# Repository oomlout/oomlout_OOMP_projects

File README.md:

# oomlout_OOMP_projects
OOpen Organization Method for parts. This is all the project details.

### Part Files
* Summaries
	Readme's are generated using mdutils (https://github.com/didix21/mdutils). Generation is done in OOMPsummaries.py
	* Readme.md (generated)  --  A summary of the part in markdown.

* Images
	Images also have extra resolutions generated these are, _140, _450, _600.
	* image.jpg  --  Main image.
	* image_RE.jpg  --  Image for size reference (usually beside a sharpened pencil).
	* image_TOP.jpg  --  Image of the top of the part.
	* image_BOTTOM.jpg  --  Image of the bottom of the part.
	
* Diagrams
	Diagrams are generated from tags, they can use templates (templates/diag/), which can use a parts tags as input. These are compiled to a python script that uses the Simple Inkscape Scripting Extension (https://github.com/spakin/SimpInkScr/) to draw and save svgs, these svgs are then used to genearate pngs, dxfs, and pdfs.
	* diagBBLS.py (generated)  --  A diagram for adding a part to a breadboard layout sheet.
	* diagDIAG.py (generated)  --  A diagram for adding a part to a layout.
	* diagIDEN.py (generated)  --  A diagram for adding a part to a PCB with details.
	* diagSCHEM.py (generated)  --  A diagram for adding a part to a schematic.
	* diagSIMP.py (generated)  --  A diagram with only the parts outline, and link.
    * diagFritz.fzpz  --  A diagram in Fritzing format
    * working.cdr  --  A file for working on the component drawing in Corel Draw format

* Datasheets
	* datasheet.pdf  --  Datasheet for the part.
	* datasheet-C-SUPL  --  If more than one datasheet exists the manufacturers four letter code is added.
	* datasheet.txt (generated)  --  If the datasheet is a duplicate this file has the location in it, if it is hosted externally a link.
	
* 3D Models
	3D models are generated programatically these routines are in OOMPscad.py, they use SolidPython (https://github.com/SolidCode/SolidPython) to generate .scad files from which stls and pngs are generated.
	* 3dmodel.scad (generated)  --  Scad model of the part. Programatically generated in OOMPscad.py
	* 3dmodel.stl (generated)  --  STL version of 3dmodel.scad
	* 3dmodel.png (generated)  --  Rendered image of 3dmodel.scad (ortho)
	
* Labels
	Labels are generated using tags and templates these are in templates/label/ they are svgs and use search and replace to generate labels. (%%ID%% is replaced by part ID and tags are format @@%%ID%%,oompPart.oompID,tagName@@). From the svgs pdfs are generated.
	* label-front.svg (generated)  --  A label for the front of a bag.
	* label-inventory.svg (generated)  --  A label for keeping inventory organized.
	* label-spec.svg (generated)  --  A label listing part specifications.

* EDA
    Design files
    * boardEagle.brd  --  Board file in Eagle format
    * schematicEagle.scm  --  Schematic File in Eagle format
    * boardKicad.brd  --  Board file in Kicad format
    * schematicKicad.scm  --  Schematic File in Kicad format

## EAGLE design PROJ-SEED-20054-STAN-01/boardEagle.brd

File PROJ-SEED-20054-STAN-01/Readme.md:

Contents
========

* [PRS20054 > ](#prs20054--)
	* [Schematic](#schematic)
	* [Interactive BOM](#interactive-bom)
	* [OOMP Parts](#oomp-parts)
	* [Images](#images)
	* [Tags](#tags)
  
![][im]
# PRS20054 > 

- ID: PROJ-SEED-20054-STAN-01
- Hex ID: PRS20054
- Name: Grove - ADXL345 - 3-Axis Digital Accelerometer(+/-16g)
- Description: Grove - ADXL345 - 3-Axis Digital Accelerometer(+/-16g)
- Long Link: [http://oom.lt/PROJ-SEED-20054-STAN-01](http://oom.lt/PROJ-SEED-20054-STAN-01)
- Short Link: [http://oom.lt/PRS20054](http://oom.lt/PRS20054)

## Schematic

## Interactive BOM

- Interactive BOM page: [ibom.html](https://htmlpreview.github.io/?https://github.com/oomlout/oomlout_OOMP_projects/blob/main/PROJ-SEED-20054-STAN-01/kicad/bom/ibom.html)

## OOMP Parts

|OOMP ID|Name|Identifier|
| :---: | :---: | :---: |
|[CAPC-0805-X-UF10-V10](https://github.com/oomlout/oomlout_OOMP_parts/tree/main/CAPC-0805-X-UF10-V10/)|[SMD (0805) 10 uF Capacitor (Ceramic) 10v](https://github.com/oomlout/oomlout_OOMP_parts/tree/main/CAPC-0805-X-UF10-V10/)|[C5, C6](https://github.com/oomlout/oomlout_OOMP_parts/tree/main/CAPC-0805-X-UF10-V10/)|
|UNMATCHED-UNMATCHED-X-UNMATCHED-01||J1, P1, P4, P5, P6, TP1, TP2, TP3, TP4|
|UNMATCHED-SO23-X-UNMATCHED-01||Q1, Q2, U5|
|[RESE-0603-X-O472-01](https://github.com/oomlout/oomlout_OOMP_parts/tree/main/RESE-0603-X-O472-01/)|[SMD (0603) 4.7k Ohm Resistor](https://github.com/oomlout/oomlout_OOMP_parts/tree/main/RESE-0603-X-O472-01/)|[R2, R3, R4, R5](https://github.com/oomlout/oomlout_OOMP_parts/tree/main/RESE-0603-X-O472-01/)|
|[SENS-LG14-X-K345-01](https://github.com/oomlout/oomlout_OOMP_parts/tree/main/SENS-LG14-X-K345-01/)|[14 Pin SMD (LGA) Digital Accelerometer (ADXL345) Sensor](https://github.com/oomlout/oomlout_OOMP_parts/tree/main/SENS-LG14-X-K345-01/)|[U1](https://github.com/oomlout/oomlout_OOMP_parts/tree/main/SENS-LG14-X-K345-01/)|

## Images

|bominteractivefront|bominteractiveback|kicadPcb3d|kicadPcb3dFront|kicadPcb3dBack|eagleSchemImage|
| :---: | :---: | :---: | :---: | :---: | :---: |
|||||||

## Tags

- oompType: PROJ
- oompSize: SEED
- oompColor: 20054
- oompDesc: STAN
- oompIndex: 01
- name: Grove - ADXL345 - 3-Axis Digital Accelerometer(+/-16g)
- gitName: 
- hexID: PRS20054
- oompID: PROJ-SEED-20054-STAN-01
- oompParts: C5,CAPC-0805-X-UF10-V10
- oompParts: C6,CAPC-0805-X-UF10-V10
- oompParts: J1,UNMATCHED-UNMATCHED-X-UNMATCHED-01
- oompParts: P1,UNMATCHED-UNMATCHED-X-UNMATCHED-01
- oompParts: P4,UNMATCHED-UNMATCHED-X-UNMATCHED-01
- oompParts: P5,UNMATCHED-UNMATCHED-X-UNMATCHED-01
- oompParts: P6,UNMATCHED-UNMATCHED-X-UNMATCHED-01
- oompParts: Q1,UNMATCHED-SO23-X-UNMATCHED-01
- oompParts: Q2,UNMATCHED-SO23-X-UNMATCHED-01
- oompParts: R2,RESE-0603-X-O472-01
- oompParts: R3,RESE-0603-X-O472-01
- oompParts: R4,RESE-0603-X-O472-01
- oompParts: R5,RESE-0603-X-O472-01
- oompParts: TP1,UNMATCHED-UNMATCHED-X-UNMATCHED-01
- oompParts: TP2,UNMATCHED-UNMATCHED-X-UNMATCHED-01
- oompParts: TP3,UNMATCHED-UNMATCHED-X-UNMATCHED-01
- oompParts: TP4,UNMATCHED-UNMATCHED-X-UNMATCHED-01
- oompParts: U1,SENS-LG14-X-K345-01
- oompParts: U5,UNMATCHED-SO23-X-UNMATCHED-01
- rawParts: C5,10uF,C-0805,C0805,Ceramic Capacitors,,
- rawParts: C6,10uF,C-0805,C0805,Ceramic Capacitors,,
- rawParts: C7,DNP,CAP-AVX-A,AVX-A,Electrolytic Capacitors,Tantalum Capacitors and Super Capacitors,,
- rawParts: J1,SMD Grove,TWIG-4P-2.0-SMD-FEMALE-REINFORCEDD,4P-SMD-2.0,,,
- rawParts: P1,,PAD-MARKANNULAR,ROUND-MARK-1.0,,DNP,
- rawParts: P2,DNP,PAD60/30,1P-65/35MIL,,,
- rawParts: P3,DNP,PAD60/30,1P-65/35MIL,,,
- rawParts: P4,,PAD-MARKANNULAR,ROUND-MARK-1.0,,DNP,
- rawParts: P5,,PAD-MARKANNULAR,ROUND-MARK-1.0,,DNP,
- rawParts: P6,,PAD-MARKANNULAR,ROUND-MARK-1.0,,DNP,
- rawParts: Q1,2N7002,MOSFET-NSOT23,SOT23,IRLL014:,,
- rawParts: Q2,2N7002,MOSFET-NSOT23,SOT23,IRLL014:,,
- rawParts: R2,4.7K,R-0603,R0603,,,
- rawParts: R3,4.7K,R-0603,R0603,,,
- rawParts: R4,4.7K,R-0603,R0603,,,
- rawParts: R5,4.7K,R-0603,R0603,,,
- rawParts: TP1,,PAD-TEST-POINT4545,TP_4545,,DNP,
- rawParts: TP2,,PAD-TEST-POINT4545,TP_4545,,DNP,
- rawParts: TP3,,PAD-TEST-POINT4545,TP_4545,,DNP,
- rawParts: TP4,,PAD-TEST-POINT4545,TP_4545,,DNP,
- rawParts: U1,ADXL345,ADXL345,LGA14,3-Axis,+/-2g / +/-4g / +/-8g / +/-16g Digital Accelerometer,,
- rawParts: U5,XC6206P252MR-G,XC6206MR,SOT23,LOW ESR Cap.Compatible Positive Voltage Regulators,,

[im]: kicadPcb3d_450.png

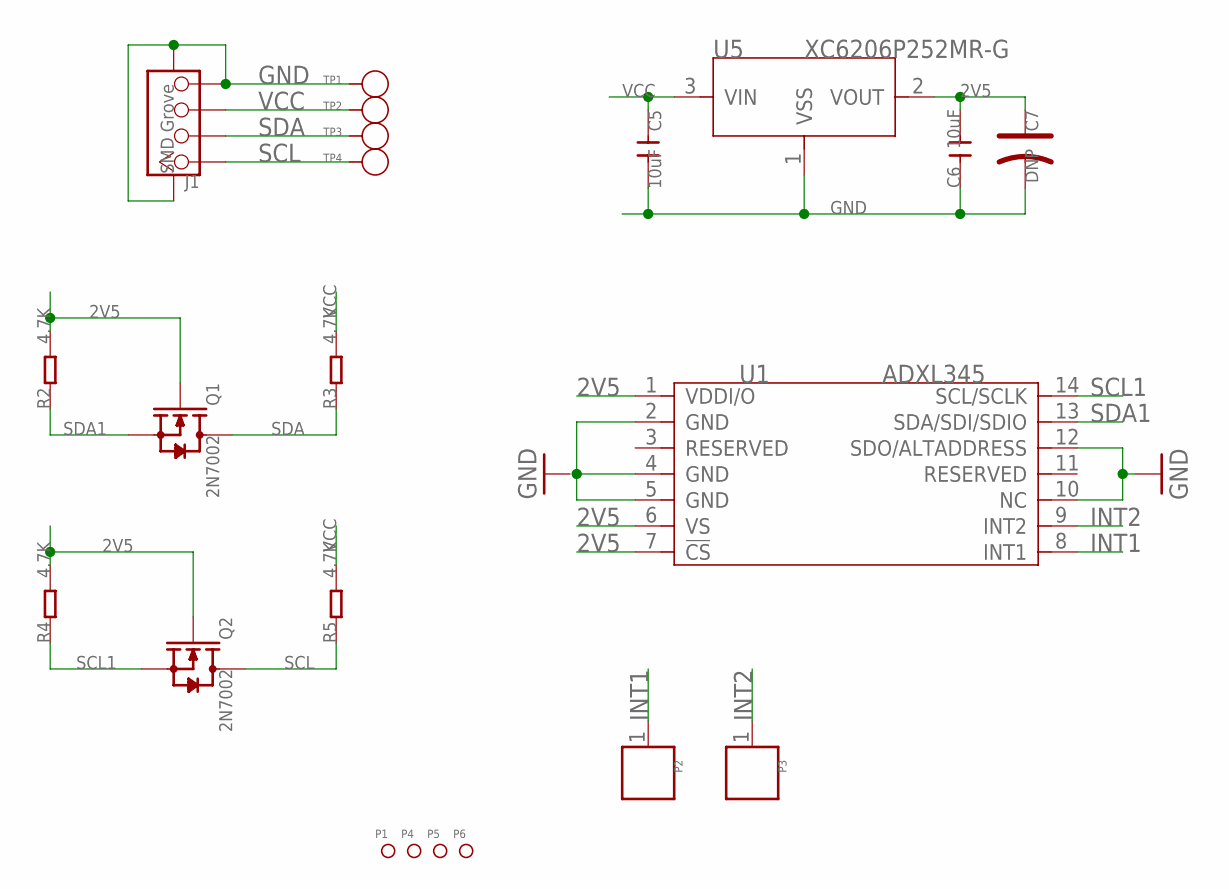
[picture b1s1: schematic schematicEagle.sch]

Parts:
C5, C6: 10uF; C0805
C7: DNP; AVX-A
J1: SMD Grove; 4P-SMD-2.0
P1, P4, P5, P6: PAD-MARK'ANNULAR'; ROUND-MARK-1.0
P2, P3: DNP; 1P-65/35MIL
Q1, Q2: 2N7002; SOT23
R2, R3, R4, R5: 4.7K; R0603
TP1, TP2, TP3, TP4: PAD-TEST-POINT'4545'; TP_4545
U1: ADXL345; LGA14
U5: XC6206P252MR-G; SOT23

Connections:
2V5: C6.2, C7.+, Q1.1 (G), Q2.1 (G), R2.2, R4.2, U1.1 (VDDI/O), U1.6 (VS), U1.7 (!CS), U5.2 (VOUT)
GND: C5.2, C6.1, C7.-, J1.4, J1.SS1, J1.SS2, TP1.T, U1.2 (GND), U1.4 (GND), U1.5 (GND), U1.10 (NC), U1.12 (SDO/ALTADDRESS), U5.1 (VSS)
INT1: P2.1, U1.8 (INT1)
INT2: P3.1, U1.9 (INT2)
SCL: J1.1, Q2.3 (D), R5.1, TP4.T
SCL1: Q2.2 (S), R4.1, U1.14 (SCL/SCLK)
SDA: J1.2, Q1.3 (D), R3.1, TP3.T
SDA1: Q1.2 (S), R2.1, U1.13 (SDA/SDI/SDIO)
VCC: C5.1, J1.3, R3.2, R5.2, TP2.T, U5.3 (VIN)

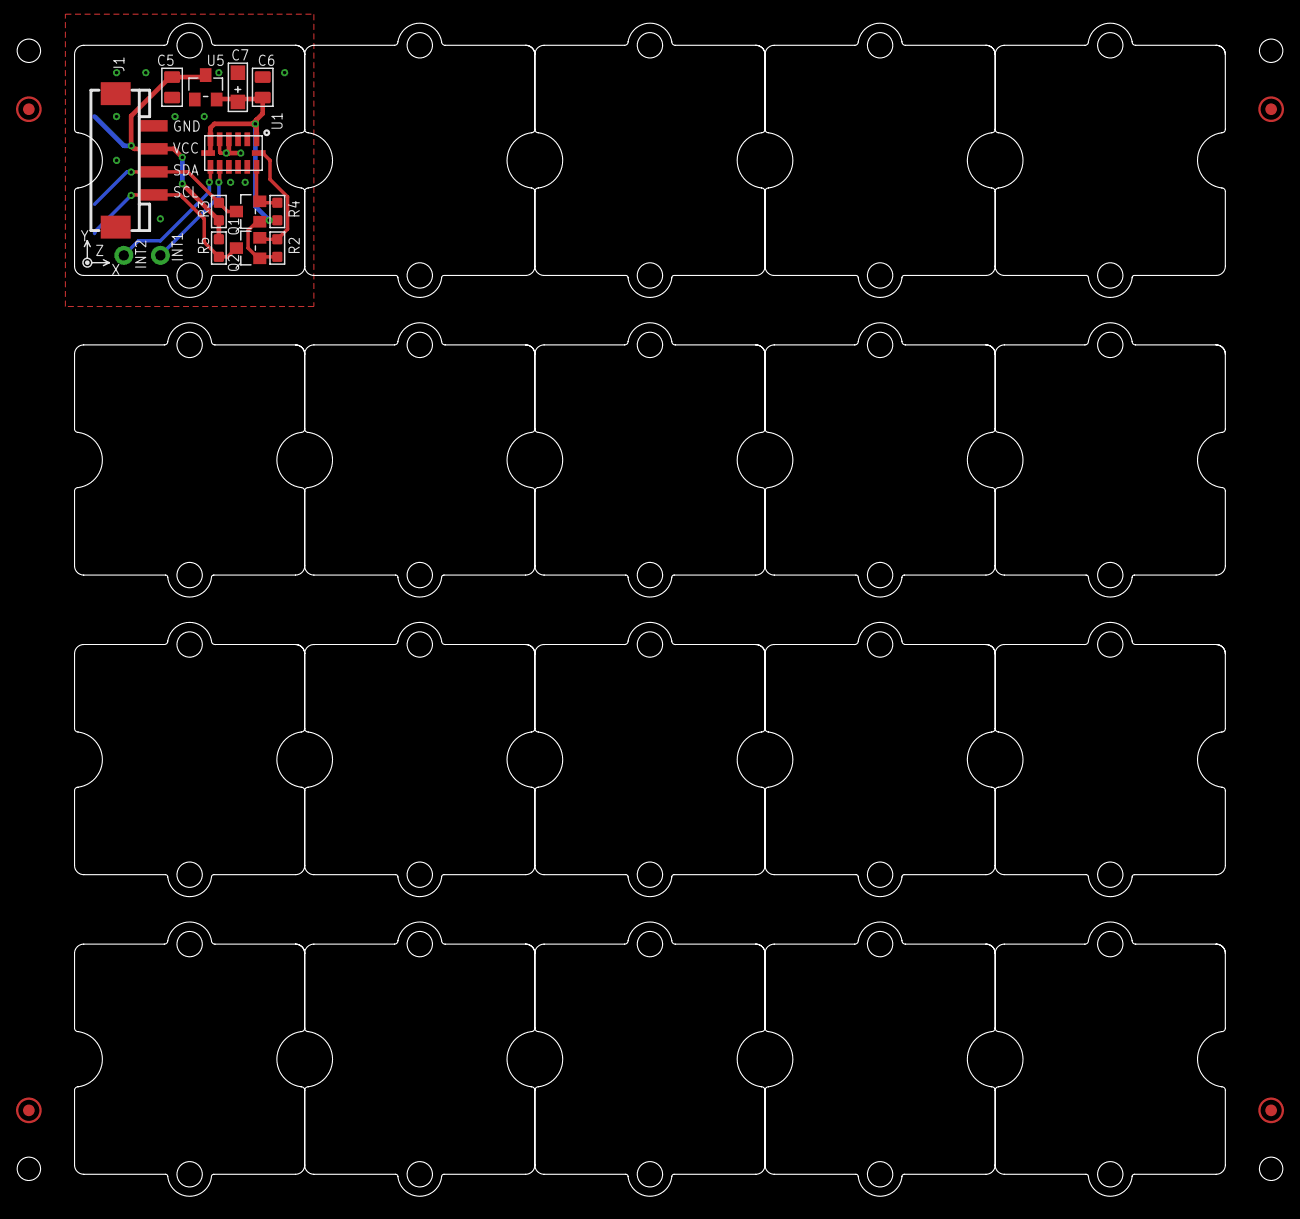
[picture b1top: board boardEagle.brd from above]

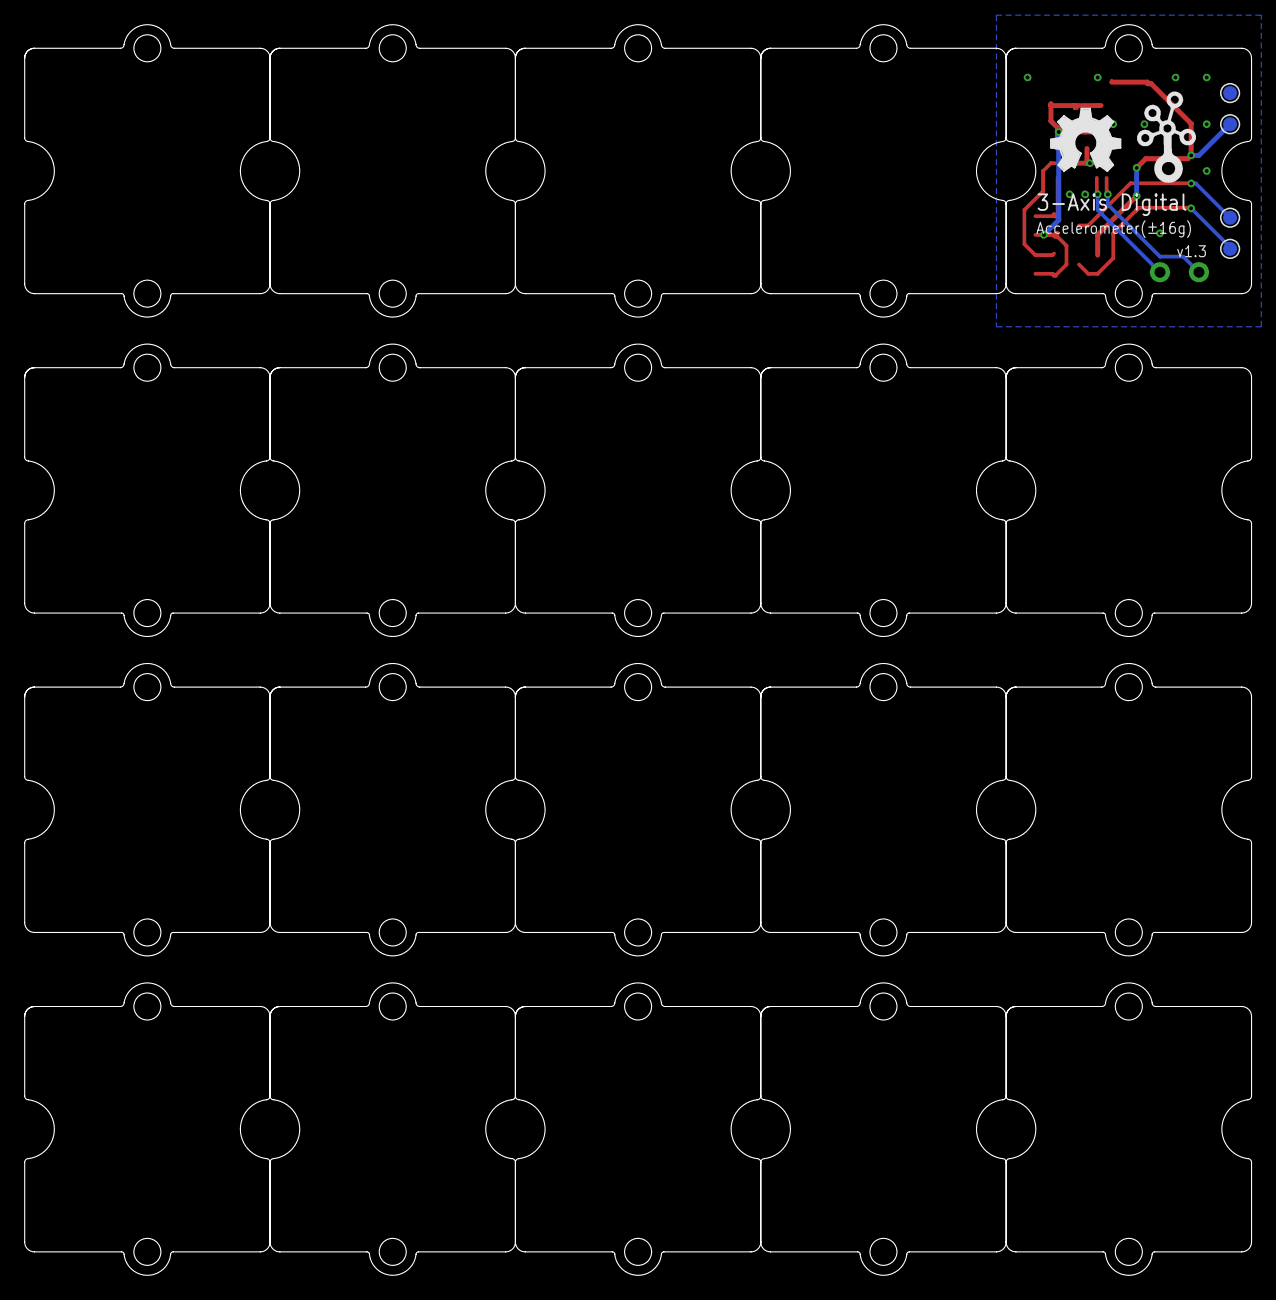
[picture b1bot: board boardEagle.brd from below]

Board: 2 copper layers, 100.0 x 101.9 mm, 44 parts (6 on the bottom side), 9 nets.

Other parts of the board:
U$1: OSHW_FILLX200_NOTEXT
U$3: TWIGLOGO
U$4, U$5, U$6, U$7, U$8, U$9, U$10, U$11, U$12, U$13, U$14, U$15, U$16, U$17, U$18, U$19, U$20, U$21, U$22, U$23: 1U-DIM-W/-DRILL

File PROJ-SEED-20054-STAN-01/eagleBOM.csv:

"Part";"Value";"Device";"Package";"Description";"PARTNO";
"C5";"10uF";"C-0805";"C0805";"Ceramic Capacitors";"";
"C6";"10uF";"C-0805";"C0805";"Ceramic Capacitors";"";
"C7";"DNP";"CAP-AVX-A";"AVX-A";"Electrolytic Capacitors,Tantalum Capacitors and Super Capacitors";"";
"J1";"SMD Grove";"TWIG-4P-2.0-SMD-FEMALE-REINFORCE'DD'";"4P-SMD-2.0";"";"";
"P1";"";"PAD-MARK'ANNULAR'";"ROUND-MARK-1.0";"";"DNP";
"P2";"DNP";"PAD'60/30'";"1P-65/35MIL";"";"";
"P3";"DNP";"PAD'60/30'";"1P-65/35MIL";"";"";
"P4";"";"PAD-MARK'ANNULAR'";"ROUND-MARK-1.0";"";"DNP";
"P5";"";"PAD-MARK'ANNULAR'";"ROUND-MARK-1.0";"";"DNP";
"P6";"";"PAD-MARK'ANNULAR'";"ROUND-MARK-1.0";"";"DNP";
"Q1";"2N7002";"MOSFET-N'SOT23'";"SOT23";"IRLL014:";"";
"Q2";"2N7002";"MOSFET-N'SOT23'";"SOT23";"IRLL014:";"";
"R2";"4.7K";"R-0603";"R0603";"";"";
"R3";"4.7K";"R-0603";"R0603";"";"";
"R4";"4.7K";"R-0603";"R0603";"";"";
"R5";"4.7K";"R-0603";"R0603";"";"";
"TP1";"";"PAD-TEST-POINT'4545'";"TP_4545";"";"DNP";
"TP2";"";"PAD-TEST-POINT'4545'";"TP_4545";"";"DNP";
"TP3";"";"PAD-TEST-POINT'4545'";"TP_4545";"";"DNP";
"TP4";"";"PAD-TEST-POINT'4545'";"TP_4545";"";"DNP";
"U1";"ADXL345";"ADXL345";"LGA14";"3-Axis,+/-2g / +/-4g / +/-8g / +/-16g Digital Accelerometer";"";
"U5";"XC6206P252MR-G";"XC6206MR";"SOT23";"LOW ESR Cap.Compatible Positive Voltage Regulators";"";

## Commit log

2022-06-14 Initial commit.
2022-06-20 New Readme.
2022-06-21 Added github harvest script and json file.
2022-07-24 Added a couple of projects.
2022-08-03 A few readme updates.
2022-08-03 Added sparkfun projects to project folder.
2022-08-03 Updated Sparkfun Projects.
2022-08-03 Added adafruit projects.
2022-08-03 Added a few more adafruit projects
2022-08-03 Added reeadme's and jsons
2022-08-03 Added new designs.
2022-08-03 A few more projects added.
2022-08-03 First try at auto generating eagle output.
2022-08-12 Exporting extra project files (through kicad)
2022-08-12 Readmes.
2022-08-14 Generated interactive BOMs.
2022-08-15 Added resolutions.
2022-08-15 added eagleIMage resolutions and fixed adafruit project oompNames.
2022-08-15 New readme's!
2022-08-17 Added pin details.
2022-08-17 Kicad bits added.
2022-08-17 First run through of part matching.
2022-08-18 Added oompParts
2022-08-21 File gen run through.
2022-08-21 Generated python parts lists.
2022-08-21 Readme test.
2022-08-21 A bit of kicad harvesting and fixed rawparts.
2022-08-21 Fixed +/- in part lists.
2022-08-21 Added parts table to readme.
2022-08-22 Finished harvesting kicad projects.
2022-08-22 Interactive boms updated.
2022-08-22 Redid part matching.
2022-08-22 A few final part changes.
2022-08-22 Image resolutions.
2022-08-23 Another parts matching run.
2022-08-23 Extra parts.
2022-08-23 New readme's and jsons.
2022-08-24 Readme's redone.
2022-08-24 Redid jsons.
2022-09-02 Project readme's sorted.
2022-09-04 Harvested schematic files for projects (some)
2022-09-04 New part files.
2022-09-04 Part file update.
2022-09-05 Change in part matching.
2022-09-06 Schematic grab finished?
2022-09-07 Added a few images and readme fixups.
2022-09-09 Higher resolution Schematics.
2022-09-10 Fixed schematic image. and updated readme.
2022-09-13 Fixed short link in readme.
2022-09-19 Attempt at part matching.
2022-09-19 Fixed up parts matching.
2022-09-21 Work on OOMP part matching.
2022-09-22 Did capacitor voltage matching.
2022-09-22 Better part representation in readme.
2022-09-22 fixing
2022-09-24 Fixed a part coding error.
2022-09-24 Part Matching refresh.
2022-09-25 A few extra details
2022-10-06 pcbdraw resolutions.
2022-10-06 Added SHEN Module Diagram.
2022-10-06 Fixed Vreg KAP2112K
2022-10-06 Changed oomp parts format.
2022-10-06 Added an ELLA
2022-10-06 Generated ELLA files.
2022-10-06 Ella update.
2022-10-07 A bit of part harvesting
2022-10-07 Added a few things.
2022-10-07 New farming.
2022-10-07 Projects updating.
2022-10-07 Fixed up readme's
2022-10-08 Part matching changes.
2022-10-08 A bit of part matching
2022-10-09 Worked on readme documenting a bit.
2022-10-10 Full prject run.
2022-10-11 Added new projects.
2022-10-12 Fixed nano schematic typo.
2022-10-12 Fixed schematic.
2022-10-13 Resolutions.
2022-10-14 Added a few project detail files properly.
2022-10-15 Current state of projects?
2022-10-15 Added a bounding box
2022-10-16 Project files
2022-10-16 Project stuff
2022-10-17 Resolutions and readme fixup.
2022-10-17 Projects refresh.
2022-10-17 Tidying up project generation.
2022-10-17 Extra matches.
2022-10-18 Some more matching.

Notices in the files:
parts and their libraries:
microbuilder: This work is placed in the public domain, and may be freely used for commercial and non-commercial work with the following conditions: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
SparkFun-Passives: Licensing: CC v3.0 Share-Alike You are welcome to use this library for commercial purposes.
